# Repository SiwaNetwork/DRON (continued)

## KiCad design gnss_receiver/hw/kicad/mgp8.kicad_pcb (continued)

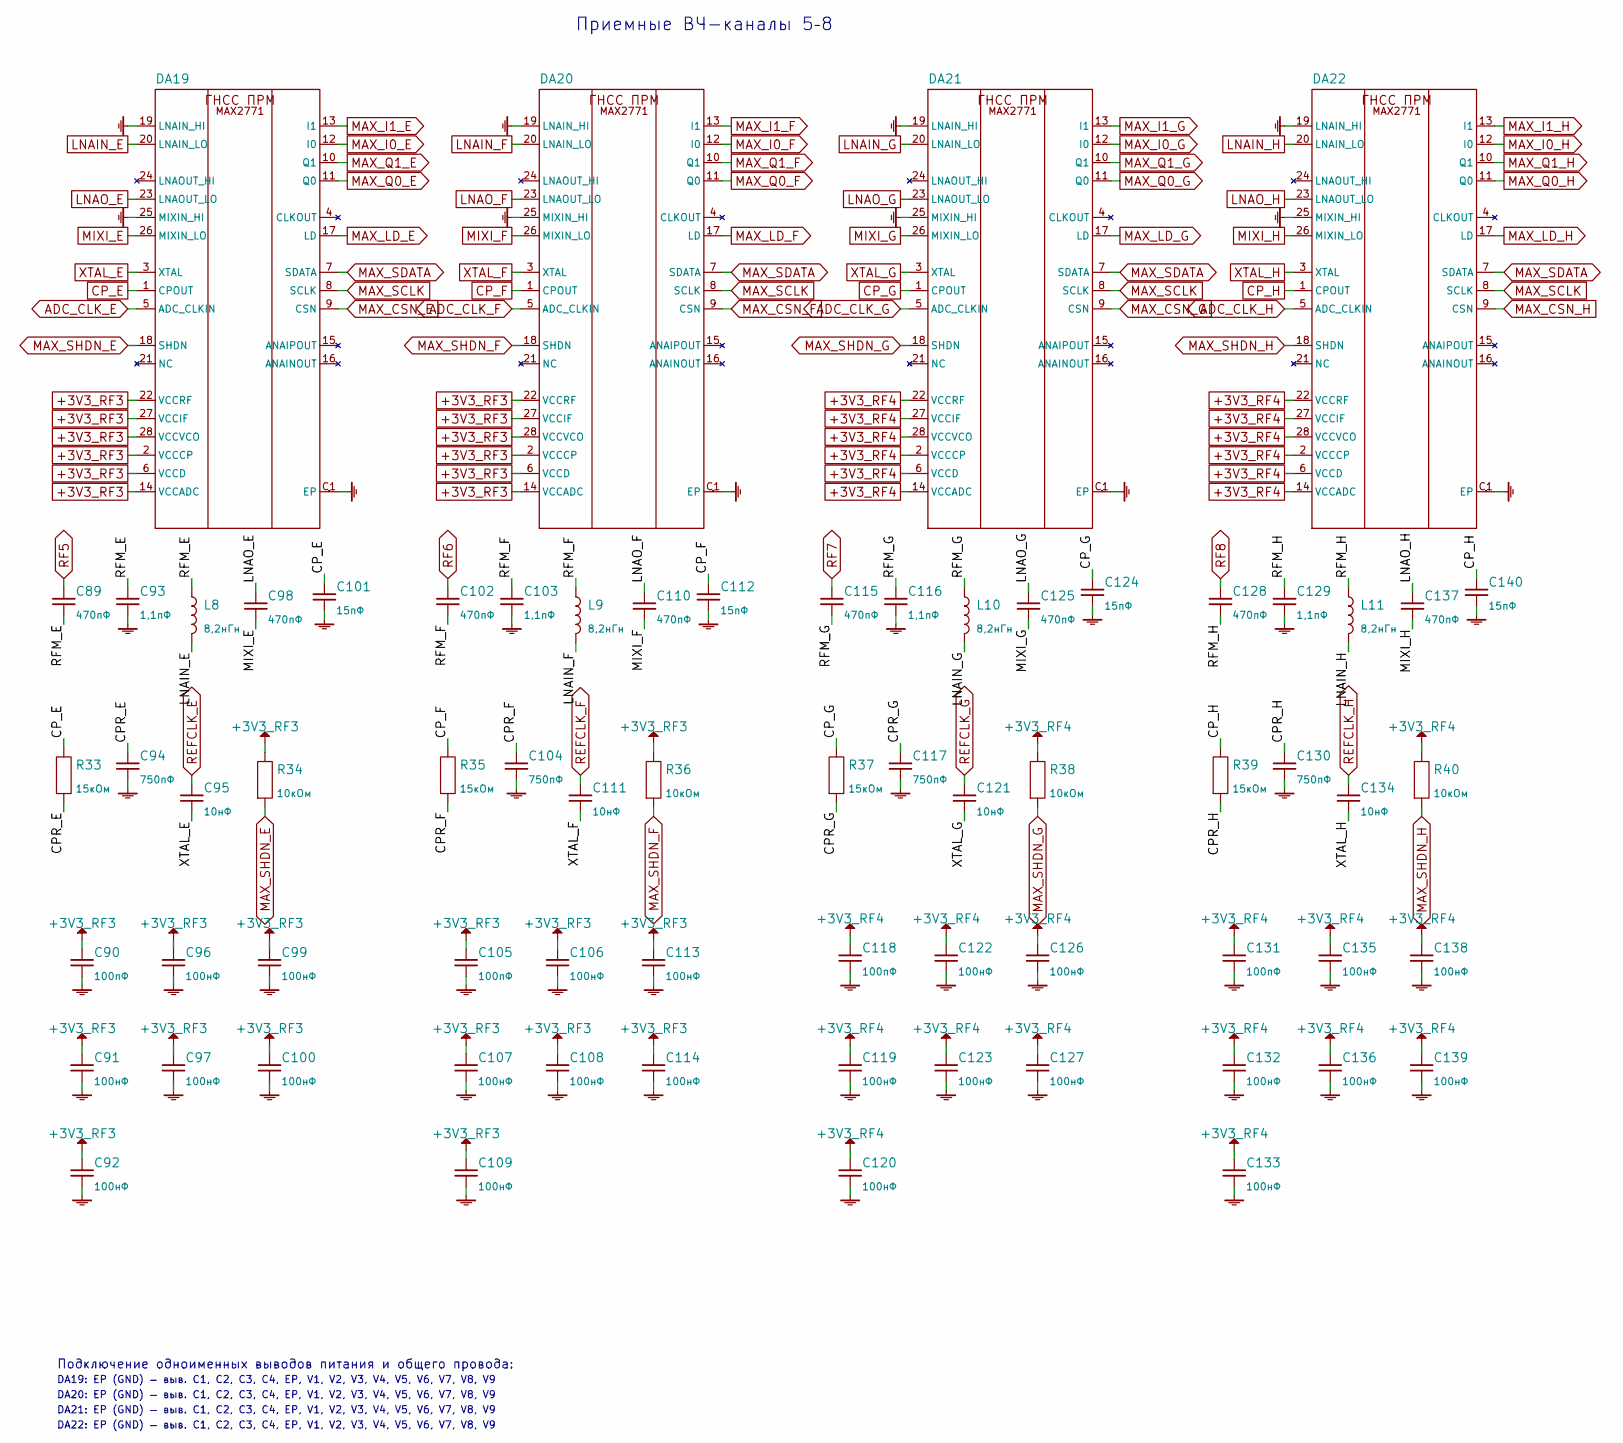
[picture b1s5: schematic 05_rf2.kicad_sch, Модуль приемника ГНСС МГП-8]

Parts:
C89, C98, C102, C110, C115, C125, C128, C137: 470пФ; C_0402_1005Metric
C90, C105, C118, C131: 100пФ; C_0402_1005Metric
C91, C92, C96, C97, C99, C100, C106, C107, C108, C109, C113, C114, C119, C120, C122, C123, C126, C127, C132, C133, C135, C136, C138, C139: 100нФ; C_0402_1005Metric
C93, C103, C116, C129: 1,1пФ; C_0402_1005Metric
C94, C104, C117, C130: 750пФ; C_0402_1005Metric
C95, C111, C121, C134: 10нФ; C_0402_1005Metric
C101, C112, C124, C140: 15пФ; C_0402_1005Metric
DA19, DA20, DA21, DA22: MAX2771ETI+; TQFN28
L8, L9, L10, L11: 8,2нГн; L_0402_1005Metric
R33, R35, R37, R39: 15кОм; R_0402_1005Metric
R34, R36, R38, R40: 10кОм; R_0402_1005Metric

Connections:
+3V3_RF3: C90.1, C91.1, C92.1, C96.1, C97.1, C99.1, C100.1, C105.1, C106.1, C107.1, C108.1, C109.1, C113.1, C114.1, DA19.2 (VCCCP), DA19.6 (VCCD), DA19.14 (VCCADC), DA19.22 (VCCRF), DA19.27 (VCCIF), DA19.28 (VCCVCO), DA20.2 (VCCCP), DA20.6 (VCCD), DA20.14 (VCCADC), DA20.22 (VCCRF), DA20.27 (VCCIF), DA20.28 (VCCVCO), R34.1, R36.1; also elsewhere on the board
+3V3_RF4: C118.1, C119.1, C120.1, C122.1, C123.1, C126.1, C127.1, C131.1, C132.1, C133.1, C135.1, C136.1, C138.1, C139.1, DA21.2 (VCCCP), DA21.6 (VCCD), DA21.14 (VCCADC), DA21.22 (VCCRF), DA21.27 (VCCIF), DA21.28 (VCCVCO), DA22.2 (VCCCP), DA22.6 (VCCD), DA22.14 (VCCADC), DA22.22 (VCCRF), DA22.27 (VCCIF), DA22.28 (VCCVCO), R38.1, R40.1; also elsewhere on the board
/Лист 5. Приемные ВЧ-каналы 5–8/CPR_E: C94.1, R33.2
/Лист 5. Приемные ВЧ-каналы 5–8/CPR_F: C104.1, R35.2
/Лист 5. Приемные ВЧ-каналы 5–8/CPR_G: C117.1, R37.2
/Лист 5. Приемные ВЧ-каналы 5–8/CPR_H: C130.1, R39.2
/Лист 5. Приемные ВЧ-каналы 5–8/RFM_E: C89.2, C93.1, L8.1
/Лист 5. Приемные ВЧ-каналы 5–8/RFM_F: C102.2, C103.1, L9.1
/Лист 5. Приемные ВЧ-каналы 5–8/RFM_G: C115.2, C116.1, L10.1
/Лист 5. Приемные ВЧ-каналы 5–8/RFM_H: C128.2, C129.1, L11.1
ADC_CLK_E: DA19.5 (ADC_CLKIN); also elsewhere on the board
ADC_CLK_F: DA20.5 (ADC_CLKIN); also elsewhere on the board
ADC_CLK_G: DA21.5 (ADC_CLKIN); also elsewhere on the board
ADC_CLK_H: DA22.5 (ADC_CLKIN); also elsewhere on the board
CP_E: C101.1, DA19.1 (CPOUT), R33.1
CP_F: C112.1, DA20.1 (CPOUT), R35.1
CP_G: C124.1, DA21.1 (CPOUT), R37.1
CP_H: C140.1, DA22.1 (CPOUT), R39.1
GND: C90.2, C91.2, C92.2, C93.2, C94.2, C96.2, C97.2, C99.2, C100.2, C101.2, C103.2, C104.2, C105.2, C106.2, C107.2, C108.2, C109.2, C112.2, C113.2, C114.2, C116.2, C117.2, C118.2, C119.2, C120.2, C122.2, C123.2, C124.2, C126.2, C127.2, C129.2, C130.2, C131.2, C132.2, C133.2, C135.2, C136.2, C138.2, C139.2, C140.2, DA19.19 (LNAIN_HI), DA19.25 (MIXIN_HI), DA19.C1 (EP), DA19.C2, DA19.C3, DA19.C4, DA19.EP, DA19.V1, DA19.V2, DA19.V3, DA19.V4, DA19.V5, DA19.V6, DA19.V7, DA19.V8, DA19.V9, DA20.19 (LNAIN_HI), DA20.25 (MIXIN_HI), DA20.C1 (EP), DA20.C2, DA20.C3, DA20.C4, DA20.EP, DA20.V1, DA20.V2, DA20.V3, DA20.V4, DA20.V5, DA20.V6, DA20.V7, DA20.V8, DA20.V9, DA21.19 (LNAIN_HI), DA21.25 (MIXIN_HI), DA21.C1 (EP), DA21.C2, DA21.C3, DA21.C4, DA21.EP, DA21.V1, DA21.V2, DA21.V3, DA21.V4, DA21.V5, DA21.V6, DA21.V7, DA21.V8, DA21.V9, DA22.19 (LNAIN_HI), DA22.25 (MIXIN_HI), DA22.C1 (EP), DA22.C2, DA22.C3, DA22.C4, DA22.EP, DA22.V1, DA22.V2, DA22.V3, DA22.V4, DA22.V5, DA22.V6, DA22.V7, DA22.V8, DA22.V9; also elsewhere on the board
LNAIN_E: DA19.20 (LNAIN_LO), L8.2
LNAIN_F: DA20.20 (LNAIN_LO), L9.2
LNAIN_G: DA21.20 (LNAIN_LO), L10.2
LNAIN_H: DA22.20 (LNAIN_LO), L11.2
LNAO_E: C98.1, DA19.23 (LNAOUT_LO)
LNAO_F: C110.1, DA20.23 (LNAOUT_LO)
LNAO_G: C125.1, DA21.23 (LNAOUT_LO)
LNAO_H: C137.1, DA22.23 (LNAOUT_LO)
MAX_CSN_E: DA19.9 (CSN); also elsewhere on the board
MAX_CSN_F: DA20.9 (CSN); also elsewhere on the board
MAX_CSN_G: DA21.9 (CSN); also elsewhere on the board
MAX_CSN_H: DA22.9 (CSN); also elsewhere on the board
MAX_I0_E: DA19.12 (I0); also elsewhere on the board
MAX_I0_F: DA20.12 (I0); also elsewhere on the board
MAX_I0_G: DA21.12 (I0); also elsewhere on the board
MAX_I0_H: DA22.12 (I0); also elsewhere on the board
MAX_I1_E: DA19.13 (I1); also elsewhere on the board
MAX_I1_F: DA20.13 (I1); also elsewhere on the board
MAX_I1_G: DA21.13 (I1); also elsewhere on the board
MAX_I1_H: DA22.13 (I1); also elsewhere on the board
MAX_LD_E: DA19.17 (LD); also elsewhere on the board
MAX_LD_F: DA20.17 (LD); also elsewhere on the board
MAX_LD_G: DA21.17 (LD); also elsewhere on the board
MAX_LD_H: DA22.17 (LD); also elsewhere on the board
MAX_Q0_E: DA19.11 (Q0); also elsewhere on the board
MAX_Q0_F: DA20.11 (Q0); also elsewhere on the board
MAX_Q0_G: DA21.11 (Q0); also elsewhere on the board
MAX_Q0_H: DA22.11 (Q0); also elsewhere on the board
MAX_Q1_E: DA19.10 (Q1); also elsewhere on the board
MAX_Q1_F: DA20.10 (Q1); also elsewhere on the board
MAX_Q1_G: DA21.10 (Q1); also elsewhere on the board
MAX_Q1_H: DA22.10 (Q1); also elsewhere on the board
MAX_SCLK: DA19.8 (SCLK), DA20.8 (SCLK), DA21.8 (SCLK), DA22.8 (SCLK); also elsewhere on the board
MAX_SDATA: DA19.7 (SDATA), DA20.7 (SDATA), DA21.7 (SDATA), DA22.7 (SDATA); also elsewhere on the board
MAX_SHDN_E: DA19.18 (SHDN), R34.2; also elsewhere on the board
MAX_SHDN_F: DA20.18 (SHDN), R36.2; also elsewhere on the board
MAX_SHDN_G: DA21.18 (SHDN), R38.2; also elsewhere on the board
MAX_SHDN_H: DA22.18 (SHDN), R40.2; also elsewhere on the board
MIXI_E: C98.2, DA19.26 (MIXIN_LO)
MIXI_F: C110.2, DA20.26 (MIXIN_LO)
MIXI_G: C125.2, DA21.26 (MIXIN_LO)
MIXI_H: C137.2, DA22.26 (MIXIN_LO)
REFCLK_E: C95.1; also elsewhere on the board
REFCLK_F: C111.1; also elsewhere on the board
REFCLK_G: C121.1; also elsewhere on the board
REFCLK_H: C134.1; also elsewhere on the board
RF5: C89.1; also elsewhere on the board
RF6: C102.1; also elsewhere on the board
RF7: C115.1; also elsewhere on the board
RF8: C128.1; also elsewhere on the board
XTAL_E: C95.2, DA19.3 (XTAL)
XTAL_F: C111.2, DA20.3 (XTAL)
XTAL_G: C121.2, DA21.3 (XTAL)
XTAL_H: C134.2, DA22.3 (XTAL)

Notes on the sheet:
Приемные ВЧ-каналы 5–8
Подключение одноименных выводов питания и общего провода:
DA19: EP (GND) — выв. C1, C2, C3, C4, EP, V1, V2, V3, V4, V5, V6, V7, V8, V9
DA20: EP (GND) — выв. C1, C2, C3, C4, EP, V1, V2, V3, V4, V5, V6, V7, V8, V9
DA21: EP (GND) — выв. C1, C2, C3, C4, EP, V1, V2, V3, V4, V5, V6, V7, V8, V9
DA22: EP (GND) — выв. C1, C2, C3, C4, EP, V1, V2, V3, V4, V5, V6, V7, V8, V9

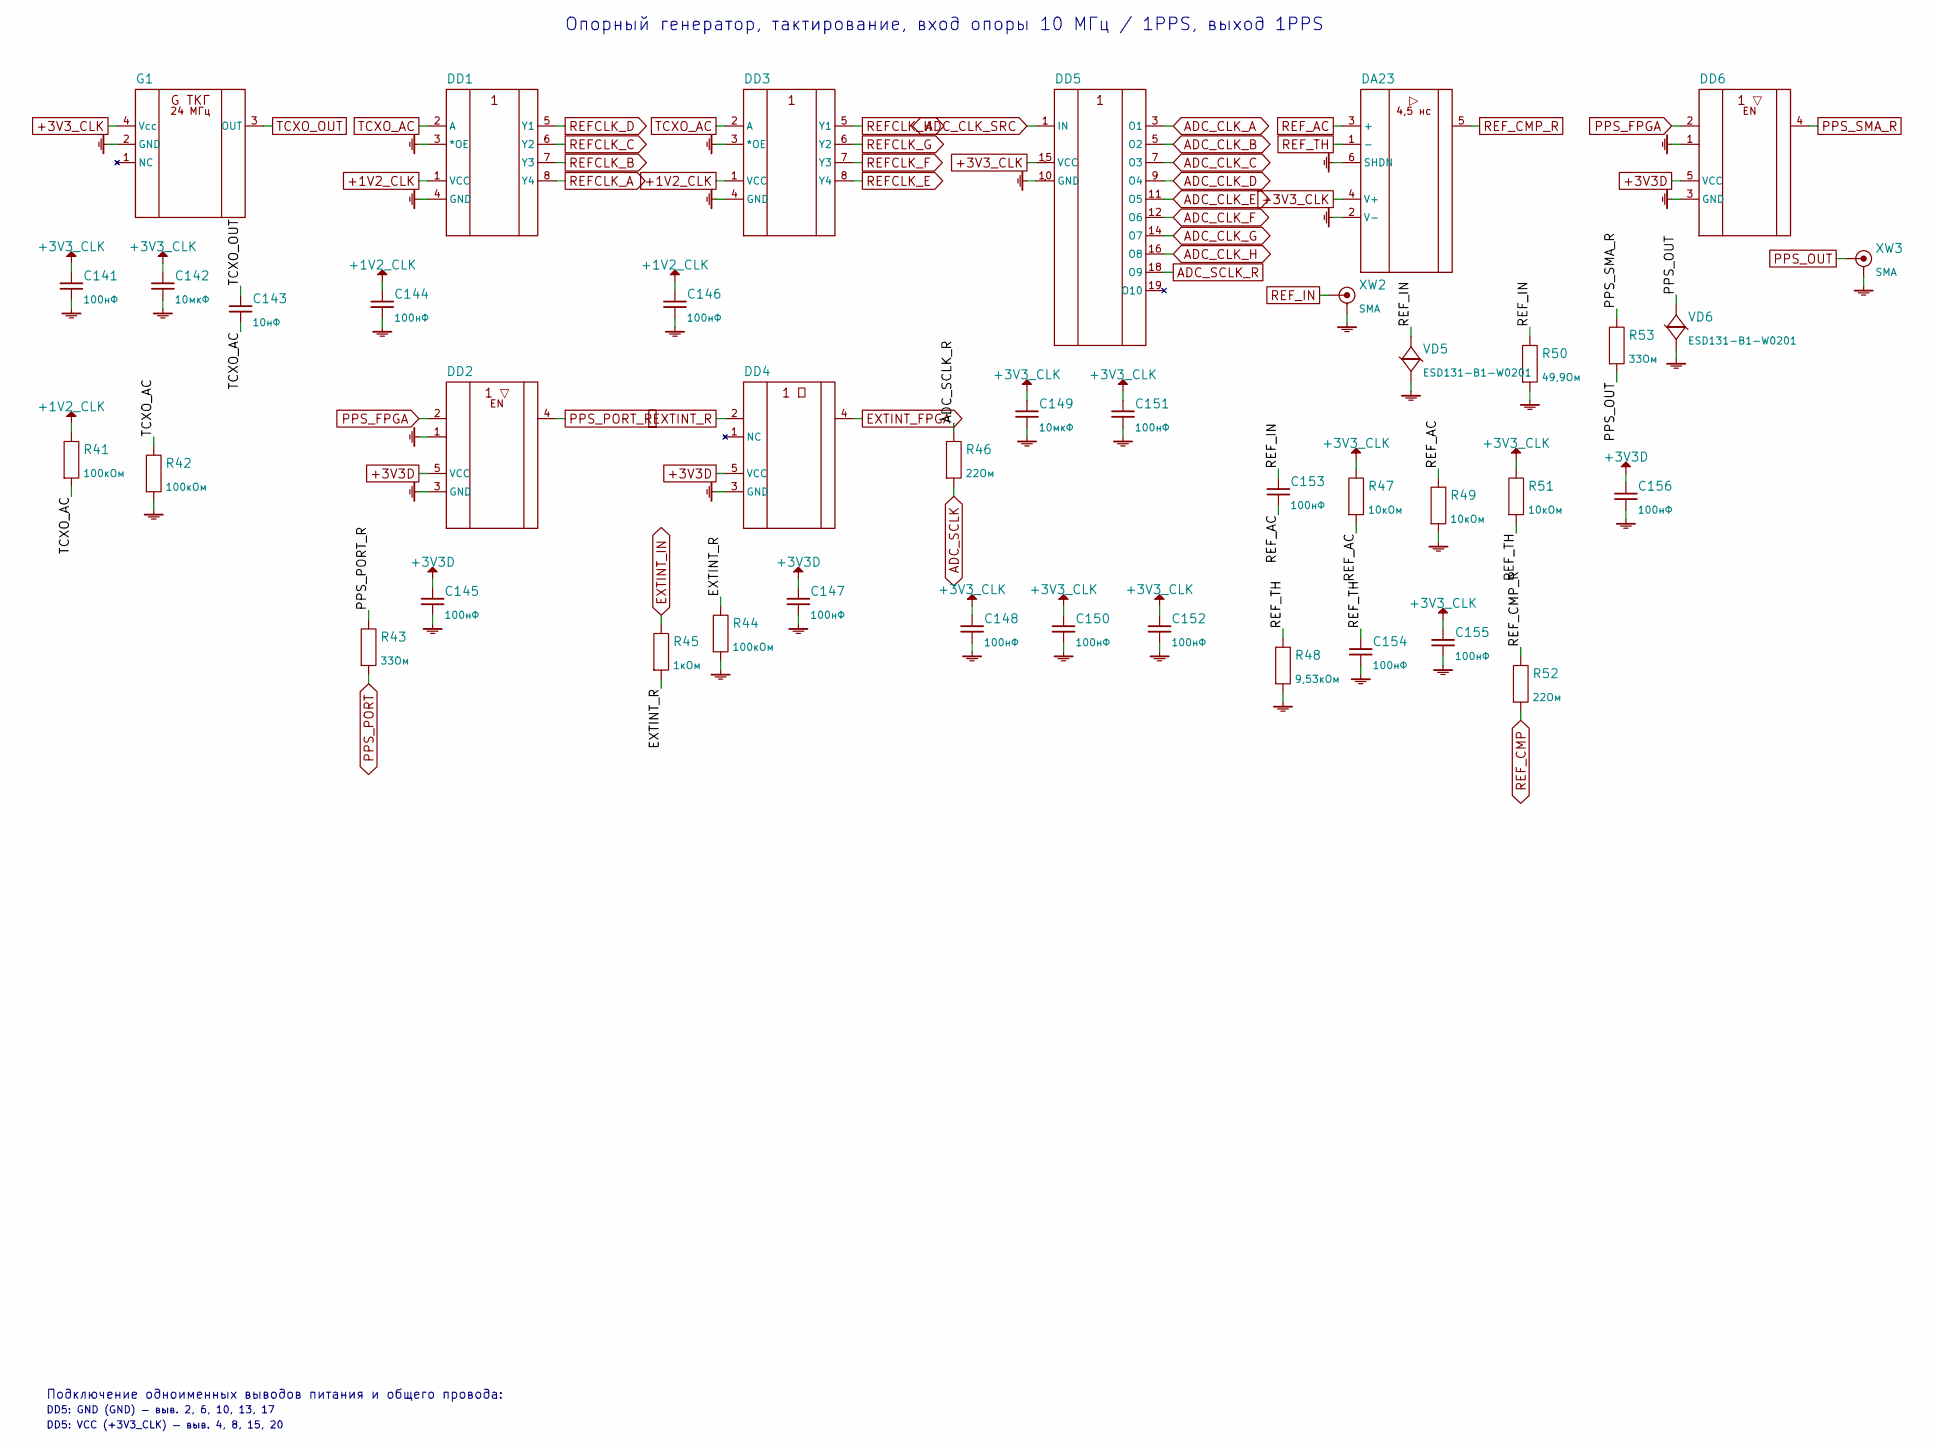
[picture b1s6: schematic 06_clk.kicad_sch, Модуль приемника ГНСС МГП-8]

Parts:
C141, C144, C145, C146, C147, C148, C150, C151, C152, C153, C154, C155, C156: 100нФ; C_0402_1005Metric
C142, C149: 10мкФ; C_0603_1608Metric
C143: 10нФ; C_0402_1005Metric
DA23: TLV3501AIDBVR; SOT-23-6
DD1, DD3: 74AVC9112DCH; VSSOP8_SOT765-1_NEX
DD2, DD6: SN74LVC1G125DBVR; SOT-23-5
DD4: SN74LVC1G17DBVR; SOT-23-5
DD5: 74FCT3807APYG; SSOP20
G1: TG2520SMN 24.0000M-MCGNNM3; TCXO
R41, R42, R44: 100кОм; R_0402_1005Metric
R43, R53: 33Ом; R_0402_1005Metric
R45: 1кОм; R_0402_1005Metric
R46, R52: 22Ом; R_0402_1005Metric
R47, R49, R51: 10кОм; R_0402_1005Metric
R48: 9,53кОм; R_0402_1005Metric
R50: 49,9Ом; R_0402_1005Metric
VD5, VD6: ESD131-B1-W0201; Infineon_SG-WLL-2-3_0.58x0.28_P0.36mm
XW2, XW3: SMA; SMA_Samtec_SMA-J-P-H-ST-EM1_EdgeMount

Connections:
+1V2_CLK: C144.1, C146.1, DD1.1 (VCC), DD3.1 (VCC), R41.1; also elsewhere on the board
+3V3D: C145.1, C147.1, C156.1, DD2.5 (VCC), DD4.5 (VCC), DD6.5 (VCC); also elsewhere on the board
+3V3_CLK: C141.1, C142.1, C148.1, C149.1, C150.1, C151.1, C152.1, C155.1, DA23.4 (V+), DD5.4, DD5.8, DD5.15 (VCC), DD5.20, G1.4 (Vcc), R47.1, R51.1; also elsewhere on the board
ADC_CLK_A: DD5.3 (O1); also elsewhere on the board
ADC_CLK_B: DD5.5 (O2); also elsewhere on the board
ADC_CLK_C: DD5.7 (O3); also elsewhere on the board
ADC_CLK_D: DD5.9 (O4); also elsewhere on the board
ADC_CLK_E: DD5.11 (O5); also elsewhere on the board
ADC_CLK_F: DD5.12 (O6); also elsewhere on the board
ADC_CLK_G: DD5.14 (O7); also elsewhere on the board
ADC_CLK_H: DD5.16 (O8); also elsewhere on the board
ADC_CLK_SRC: DD5.1 (IN); also elsewhere on the board
ADC_SCLK: R46.2; also elsewhere on the board
ADC_SCLK_R: DD5.18 (O9), R46.1
EXTINT_FPGA: DD4.4; also elsewhere on the board
EXTINT_IN: R45.1; also elsewhere on the board
EXTINT_R: DD4.2, R44.1, R45.2
GND: C141.2, C142.2, C144.2, C145.2, C146.2, C147.2, C148.2, C149.2, C150.2, C151.2, C152.2, C154.2, C155.2, C156.2, DA23.2 (V-), DA23.6 (SHDN), DD1.3 (*OE), DD1.4 (GND), DD2.1, DD2.3 (GND), DD3.3 (*OE), DD3.4 (GND), DD4.3 (GND), DD5.2, DD5.6, DD5.10 (GND), DD5.13, DD5.17, DD6.1, DD6.3 (GND), G1.2 (GND), R42.2, R44.2, R48.2, R49.2, R50.2, VD5.2, VD6.2, XW2.2, XW3.2; also elsewhere on the board
PPS_FPGA: DD2.2, DD6.2; also elsewhere on the board
PPS_OUT: R53.2, VD6.1, XW3.1
PPS_PORT: R43.2; also elsewhere on the board
PPS_PORT_R: DD2.4, R43.1
PPS_SMA_R: DD6.4, R53.1
REFCLK_A: DD1.8 (Y4); also elsewhere on the board
REFCLK_B: DD1.7 (Y3); also elsewhere on the board
REFCLK_C: DD1.6 (Y2); also elsewhere on the board
REFCLK_D: DD1.5 (Y1); also elsewhere on the board
REFCLK_E: DD3.8 (Y4); also elsewhere on the board
REFCLK_F: DD3.7 (Y3); also elsewhere on the board
REFCLK_G: DD3.6 (Y2); also elsewhere on the board
REFCLK_H: DD3.5 (Y1); also elsewhere on the board
REF_AC: C153.2, DA23.3 (+), R47.2, R49.1
REF_CMP: R52.2; also elsewhere on the board
REF_CMP_R: DA23.5, R52.1
REF_IN: C153.1, R50.1, VD5.1, XW2.1
REF_TH: C154.1, DA23.1 (-), R48.1, R51.2
TCXO_AC: C143.2, DD1.2 (A), DD3.2 (A), R41.2, R42.1
TCXO_OUT: C143.1, G1.3 (OUT)

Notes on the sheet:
Опорный генератор, тактирование, вход опоры 10 МГц / 1PPS, выход 1PPS
Подключение одноименных выводов питания и общего провода:
DD5: GND (GND) — выв. 2, 6, 10, 13, 17
DD5: VCC (+3V3_CLK) — выв. 4, 8, 15, 20

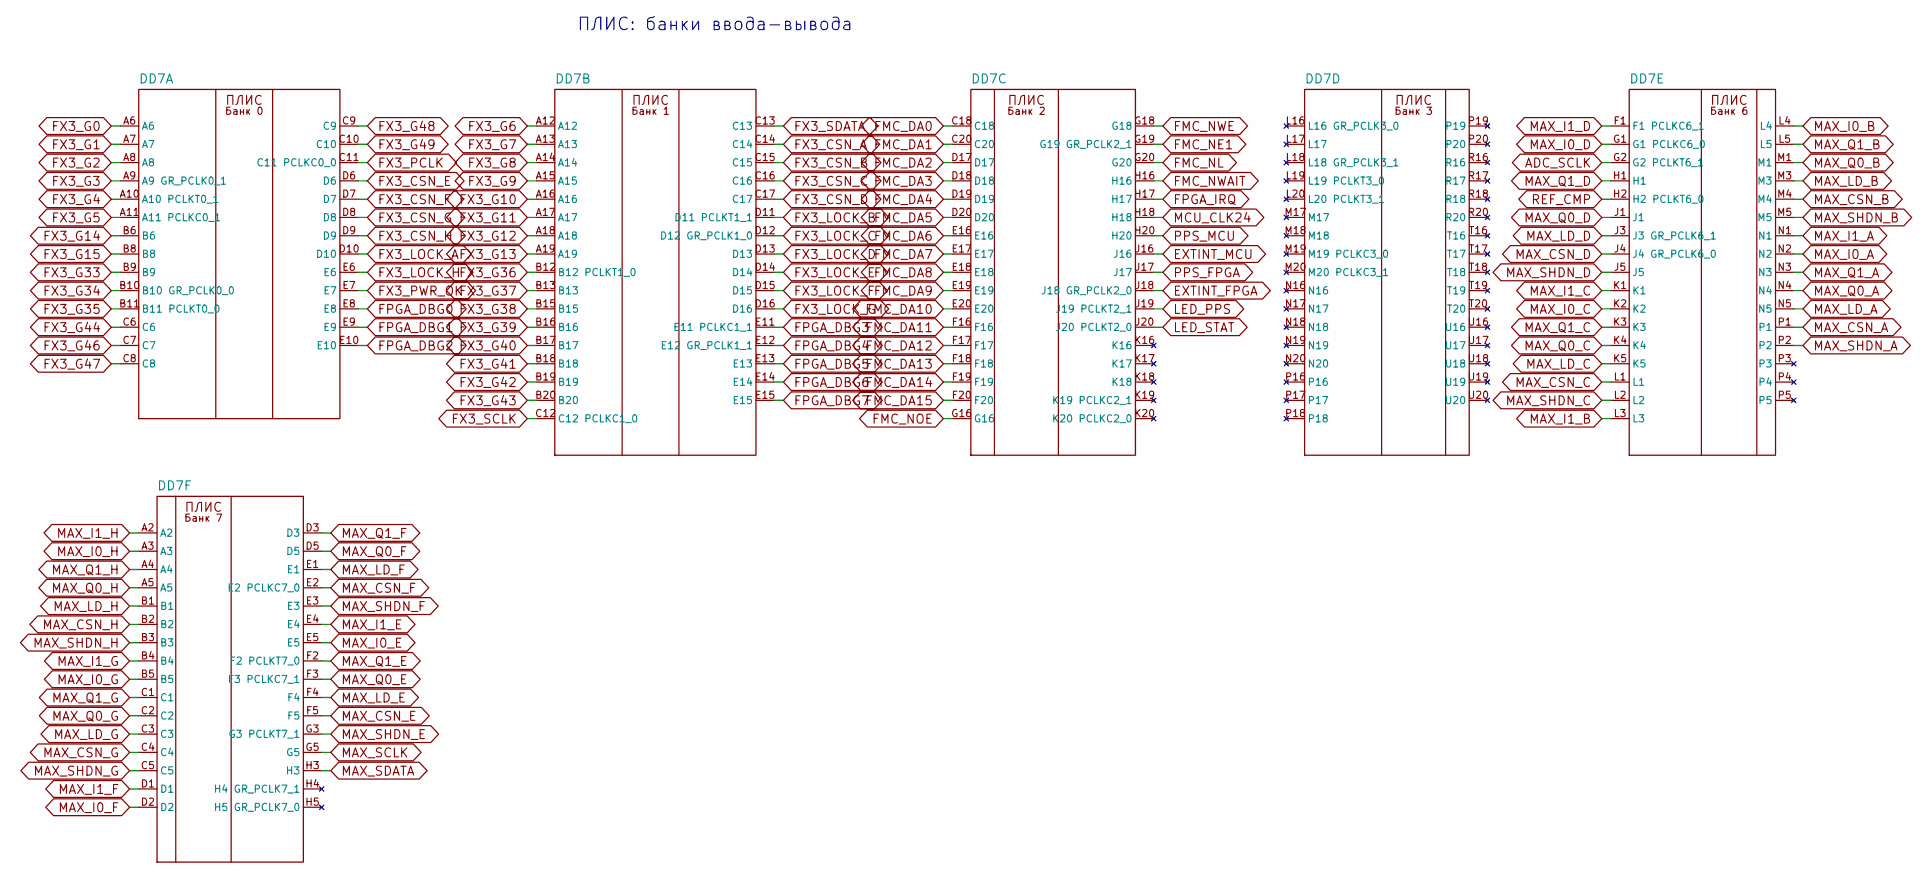
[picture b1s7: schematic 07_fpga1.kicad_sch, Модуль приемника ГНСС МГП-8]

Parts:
DD7: LFE5U-45F-6BG381I; Lattice_caBGA-381_17x17mm_Layout20x20_P0.8mm

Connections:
ADC_SCLK: DD7.G2 (G2 PCLKT6_1); also elsewhere on the board
EXTINT_FPGA: DD7.J18 (J18 GR_PCLK2_0); also elsewhere on the board
EXTINT_MCU: DD7.J16; also elsewhere on the board
FMC_DA0: DD7.C18; also elsewhere on the board
FMC_DA1: DD7.C20; also elsewhere on the board
FMC_DA2: DD7.D17; also elsewhere on the board
FMC_DA3: DD7.D18; also elsewhere on the board
FMC_DA4: DD7.D19; also elsewhere on the board
FMC_DA5: DD7.D20; also elsewhere on the board
FMC_DA6: DD7.E16; also elsewhere on the board
FMC_DA7: DD7.E17; also elsewhere on the board
FMC_DA8: DD7.E18; also elsewhere on the board
FMC_DA9: DD7.E19; also elsewhere on the board
FMC_DA10: DD7.E20; also elsewhere on the board
FMC_DA11: DD7.F16; also elsewhere on the board
FMC_DA12: DD7.F17; also elsewhere on the board
FMC_DA13: DD7.F18; also elsewhere on the board
FMC_DA14: DD7.F19; also elsewhere on the board
FMC_DA15: DD7.F20; also elsewhere on the board
FMC_NE1: DD7.G19 (G19 GR_PCLK2_1); also elsewhere on the board
FMC_NL: DD7.G20; also elsewhere on the board
FMC_NOE: DD7.G16; also elsewhere on the board
FMC_NWAIT: DD7.H16; also elsewhere on the board
FMC_NWE: DD7.G18; also elsewhere on the board
FPGA_DBG0: DD7.E8; also elsewhere on the board
FPGA_DBG1: DD7.E9; also elsewhere on the board
FPGA_DBG2: DD7.E10; also elsewhere on the board
FPGA_DBG3: DD7.E11 (E11 PCLKC1_1); also elsewhere on the board
FPGA_DBG4: DD7.E12 (E12 GR_PCLK1_1); also elsewhere on the board
FPGA_DBG5: DD7.E13; also elsewhere on the board
FPGA_DBG6: DD7.E14; also elsewhere on the board
FPGA_DBG7: DD7.E15; also elsewhere on the board
FPGA_IRQ: DD7.H17; also elsewhere on the board
FX3_CSN_A: DD7.C14; also elsewhere on the board
FX3_CSN_B: DD7.C15; also elsewhere on the board
FX3_CSN_C: DD7.C16; also elsewhere on the board
FX3_CSN_D: DD7.C17; also elsewhere on the board
FX3_CSN_E: DD7.D6; also elsewhere on the board
FX3_CSN_F: DD7.D7; also elsewhere on the board
FX3_CSN_G: DD7.D8; also elsewhere on the board
FX3_CSN_H: DD7.D9; also elsewhere on the board
FX3_G0: DD7.A6; also elsewhere on the board
FX3_G1: DD7.A7; also elsewhere on the board
FX3_G2: DD7.A8; also elsewhere on the board
FX3_G3: DD7.A9 (A9 GR_PCLK0_1); also elsewhere on the board
FX3_G4: DD7.A10 (A10 PCLKT0_1); also elsewhere on the board
FX3_G5: DD7.A11 (A11 PCLKC0_1); also elsewhere on the board
FX3_G6: DD7.A12; also elsewhere on the board
FX3_G7: DD7.A13; also elsewhere on the board
FX3_G8: DD7.A14; also elsewhere on the board
FX3_G9: DD7.A15; also elsewhere on the board
FX3_G10: DD7.A16; also elsewhere on the board
FX3_G11: DD7.A17; also elsewhere on the board
FX3_G12: DD7.A18; also elsewhere on the board
FX3_G13: DD7.A19; also elsewhere on the board
FX3_G14: DD7.B6; also elsewhere on the board
FX3_G15: DD7.B8; also elsewhere on the board
FX3_G33: DD7.B9; also elsewhere on the board
FX3_G34: DD7.B10 (B10 GR_PCLK0_0); also elsewhere on the board
FX3_G35: DD7.B11 (B11 PCLKT0_0); also elsewhere on the board
FX3_G36: DD7.B12 (B12 PCLKT1_0); also elsewhere on the board
FX3_G37: DD7.B13; also elsewhere on the board
FX3_G38: DD7.B15; also elsewhere on the board
FX3_G39: DD7.B16; also elsewhere on the board
FX3_G40: DD7.B17; also elsewhere on the board
FX3_G41: DD7.B18; also elsewhere on the board
FX3_G42: DD7.B19; also elsewhere on the board
FX3_G43: DD7.B20; also elsewhere on the board
FX3_G44: DD7.C6; also elsewhere on the board
FX3_G46: DD7.C7; also elsewhere on the board
FX3_G47: DD7.C8; also elsewhere on the board
FX3_G48: DD7.C9; also elsewhere on the board
FX3_G49: DD7.C10; also elsewhere on the board
FX3_LOCK_A: DD7.D10; also elsewhere on the board
FX3_LOCK_B: DD7.D11 (D11 PCLKT1_1); also elsewhere on the board
FX3_LOCK_C: DD7.D12 (D12 GR_PCLK1_0); also elsewhere on the board
FX3_LOCK_D: DD7.D13; also elsewhere on the board
FX3_LOCK_E: DD7.D14; also elsewhere on the board
FX3_LOCK_F: DD7.D15; also elsewhere on the board
FX3_LOCK_G: DD7.D16; also elsewhere on the board
FX3_LOCK_H: DD7.E6; also elsewhere on the board
FX3_PCLK: DD7.C11 (C11 PCLKC0_0); also elsewhere on the board
FX3_PWR_OK: DD7.E7; also elsewhere on the board
FX3_SCLK: DD7.C12 (C12 PCLKC1_0); also elsewhere on the board
FX3_SDATA: DD7.C13; also elsewhere on the board
LED_PPS: DD7.J19 (J19 PCLKT2_1); also elsewhere on the board
LED_STAT: DD7.J20 (J20 PCLKT2_0); also elsewhere on the board
MAX_CSN_A: DD7.P1; also elsewhere on the board
MAX_CSN_B: DD7.M4; also elsewhere on the board
MAX_CSN_C: DD7.L1; also elsewhere on the board
MAX_CSN_D: DD7.J4 (J4 GR_PCLK6_0); also elsewhere on the board
MAX_CSN_E: DD7.F5; also elsewhere on the board
MAX_CSN_F: DD7.E2 (E2 PCLKC7_0); also elsewhere on the board
MAX_CSN_G: DD7.C4; also elsewhere on the board
MAX_CSN_H: DD7.B2; also elsewhere on the board
MAX_I0_A: DD7.N2; also elsewhere on the board
MAX_I0_B: DD7.L4; also elsewhere on the board
MAX_I0_C: DD7.K2; also elsewhere on the board
MAX_I0_D: DD7.G1 (G1 PCLKC6_0); also elsewhere on the board
MAX_I0_E: DD7.E5; also elsewhere on the board
MAX_I0_F: DD7.D2; also elsewhere on the board
MAX_I0_G: DD7.B5; also elsewhere on the board
MAX_I0_H: DD7.A3; also elsewhere on the board
MAX_I1_A: DD7.N1; also elsewhere on the board
MAX_I1_B: DD7.L3; also elsewhere on the board
MAX_I1_C: DD7.K1; also elsewhere on the board
MAX_I1_D: DD7.F1 (F1 PCLKC6_1); also elsewhere on the board
MAX_I1_E: DD7.E4; also elsewhere on the board
MAX_I1_F: DD7.D1; also elsewhere on the board
MAX_I1_G: DD7.B4; also elsewhere on the board
MAX_I1_H: DD7.A2; also elsewhere on the board
MAX_LD_A: DD7.N5; also elsewhere on the board
MAX_LD_B: DD7.M3; also elsewhere on the board
MAX_LD_C: DD7.K5; also elsewhere on the board
MAX_LD_D: DD7.J3 (J3 GR_PCLK6_1); also elsewhere on the board
MAX_LD_E: DD7.F4; also elsewhere on the board
MAX_LD_F: DD7.E1; also elsewhere on the board
MAX_LD_G: DD7.C3; also elsewhere on the board
MAX_LD_H: DD7.B1; also elsewhere on the board
MAX_Q0_A: DD7.N4; also elsewhere on the board
MAX_Q0_B: DD7.M1; also elsewhere on the board
MAX_Q0_C: DD7.K4; also elsewhere on the board
MAX_Q0_D: DD7.J1; also elsewhere on the board
MAX_Q0_E: DD7.F3 (F3 PCLKC7_1); also elsewhere on the board
MAX_Q0_F: DD7.D5; also elsewhere on the board
MAX_Q0_G: DD7.C2; also elsewhere on the board
MAX_Q0_H: DD7.A5; also elsewhere on the board
MAX_Q1_A: DD7.N3; also elsewhere on the board
MAX_Q1_B: DD7.L5; also elsewhere on the board
MAX_Q1_C: DD7.K3; also elsewhere on the board
MAX_Q1_D: DD7.H1; also elsewhere on the board
MAX_Q1_E: DD7.F2 (F2 PCLKT7_0); also elsewhere on the board
MAX_Q1_F: DD7.D3; also elsewhere on the board
MAX_Q1_G: DD7.C1; also elsewhere on the board
MAX_Q1_H: DD7.A4; also elsewhere on the board
MAX_SCLK: DD7.G5; also elsewhere on the board
MAX_SDATA: DD7.H3; also elsewhere on the board
MAX_SHDN_A: DD7.P2; also elsewhere on the board
MAX_SHDN_B: DD7.M5; also elsewhere on the board
MAX_SHDN_C: DD7.L2; also elsewhere on the board
MAX_SHDN_D: DD7.J5; also elsewhere on the board
MAX_SHDN_E: DD7.G3 (G3 PCLKT7_1); also elsewhere on the board
MAX_SHDN_F: DD7.E3; also elsewhere on the board
MAX_SHDN_G: DD7.C5; also elsewhere on the board
MAX_SHDN_H: DD7.B3; also elsewhere on the board
MCU_CLK24: DD7.H18; also elsewhere on the board
PPS_FPGA: DD7.J17; also elsewhere on the board
PPS_MCU: DD7.H20; also elsewhere on the board
REF_CMP: DD7.H2 (H2 PCLKT6_0); also elsewhere on the board

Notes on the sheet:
ПЛИС: банки ввода-вывода
